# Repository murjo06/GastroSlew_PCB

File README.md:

# GastroSlew_PCB
PCB deisng files for GastroSlew, running FOC

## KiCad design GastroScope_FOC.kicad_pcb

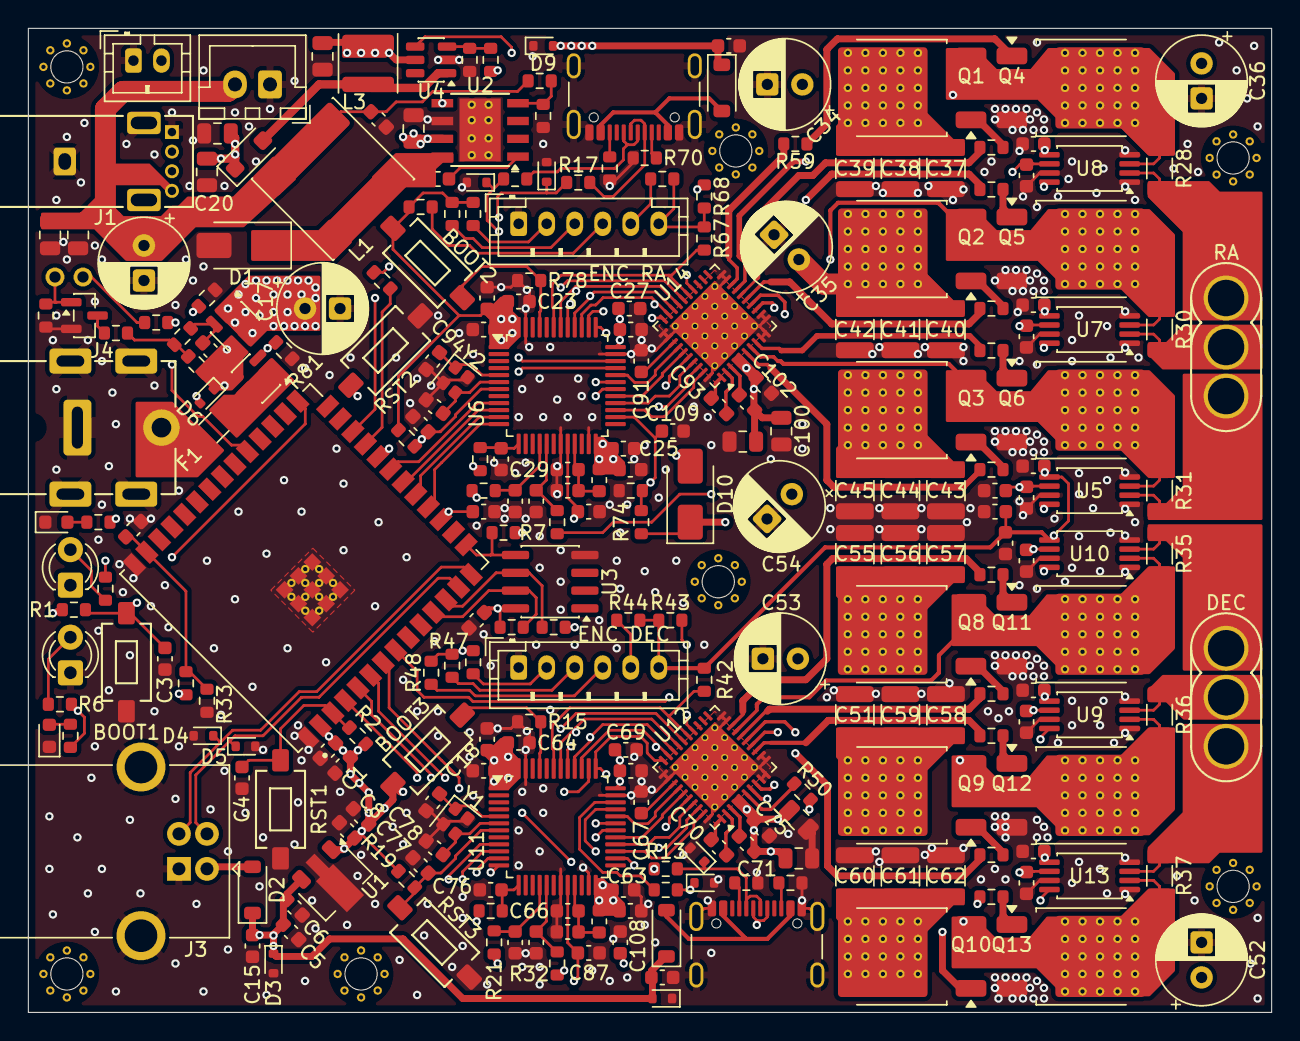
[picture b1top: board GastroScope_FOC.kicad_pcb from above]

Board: 4 copper layers, 88.8 x 70.2 mm, 257 parts (0 on the bottom side), 154 nets.

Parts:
BOOT1, BOOT2, BOOT3: TS3625X; SW_SPST_6.0x3.5
C1, C5, C8, C15, C16, C26, C27, C28, C30, C50, C68, C69, C72, C80, C98, C105, C107: 10u; C_0603_1608Metric
C2, C3, C4, C6, C7, C18, C19, C22, C23, C24, C25, C29, C31, C32, C46, C47, C49, C63, C64, C65, C66, C75, C77, C81, C82, C83, C87, C88, C89, C90, C92, C99, C102, C104: 100n; C_0603_1608Metric
C9: 2u2; C_0603_1608Metric
C10, C103, C106, C108, C109: 10n; C_0603_1608Metric
C11, C20, C21, C73, C85, C86, C100, C101: 10u; C_0805_2012Metric
C12, C13: 22u; C_0805_2012Metric
C14, C17, C34, C35, C36, C52, C53, C54: 330u; CP_Radial_D6.3mm_P2.50mm
C33, C48, C74, C76, C84, C97: 2n2; C_0603_1608Metric
C37, C38, C39, C40, C41, C42, C43, C44, C45, C51, C55, C56, C57, C58, C59, C60, C61, C62: 22u; C_1210_3225Metric
C67, C71, C91, C96: 1u; C_0603_1608Metric
C70, C93: 47n; C_0603_1608Metric
C78, C79, C94, C95: 12p; C_0603_1608Metric
D1, D10: SS34; D_SMA
D2, D12, D18: 1N5819HW-7-F; D_SOD-123
D3, D4, D5, D9, D13, D14, D17, D19, D20: LESD5D5.0CT1G; D_SOD-523
D6: BZT52C12T; D_SOD-523
D7, D15: LED; LED_0603_1608Metric
D8, D16: LED; LED_D3.0mm
D11: DSS34; D_SOD-123F
F1: 4A; Fuse_1206_3216Metric
J1: USB_A; USB_A_sideways
J2: VOUT; JST_XH_B2B-XH-A_1x02_P2.50mm_Vertical
J3: USB_B; USB_B_OST_USB-B1HSxx_Horizontal
J4: VIN; Connector_BarrelJack_HighCurrent
J5, J9: MOTOR; Connector_MR-30
J6, J8: USB_C_Receptacle_USB2.0_14P; USB_C_Receptacle_GCT_USB4105-xx-A_16P_TopMnt_Horizontal
J7, J10: ENCODER; JST_PH_B6B-PH-K_1x06_P2.00mm_Vertical
L1: 15u; L_APV_ANR8040
L2, L5: 120R; L_0603_1608Metric
L3: 15u; L_APV_ANR4030
L4: BRAKE; JST_PH_B2B-PH-K_1x02_P2.00mm_Vertical
MCU1: ESP32-S3-WROOM-1U; XCVR_ESP32-S3-WROOM-1U-N4R2
Q1, Q2, Q3, Q4, Q5, Q6, Q8, Q9, Q10, Q11, Q12, Q13: IRLR7821TRLPBF; DPAK_TO-252
Q7: AO3400A; SOT-23
Q14, Q15: SP40P28TS; STO-23-6-PMOS
R1, R2, R3, R9, R15, R19, R41, R42, R43, R44, R47, R48, R66, R67, R68, R69, R72, R73, R78, R79, R80: 10k; R_0603_1608Metric
R4: 3k24; R_0603_1608Metric
R5, R6, R89: 330R; R_0603_1608Metric
R7, R8: 4k7; R_0603_1608Metric
R10, R25: 1k; R_0603_1608Metric
R11, R26, R27, R74, R81, R86, R87, R88: 100k; R_0603_1608Metric
R12: 2k55; R_0603_1608Metric
R13, R14, R17, R18: 22R; R_0603_1608Metric
R16, R20, R21, R29, R32, R65: 100R; R_0603_1608Metric
R22, R23, R24, R49, R50, R51, R52, R53, R54, R59, R60, R61: 4R7; R_0603_1608Metric
R28, R30, R31, R35, R36, R37: R50; R_1206_3216Metric
R33, R75: 6k8; R_0603_1608Metric
R34: 0; R_0603_1608Metric
R45, R46, R70, R71: 5k1; R_0603_1608Metric
RST1, RST2, RST3: TS3625X; SW_SPST_6.0x3.5
SW1: EN; PinHeader_1x02_P2.00mm_Vertical
U1: MD7671E33PA1; SOT-89-3
U2: TPS5430DDAR; TI_SO-PowerPAD-8_ThermalVias
U3: M24C64-RMN6TP; SOIC-8_3.9x4.9mm_P1.27mm
U4: MT3608; SOT-23-6
U5, U7, U8, U9, U10, U13: INA240AxPW; TSSOP-8_4.4x3mm_P0.65mm
U6, U11: STM32G474CBTx; LQFP-48_7x7mm_P0.5mm
U12, U14: DRV8323S; QFN-40-1EP_6x6mm_P0.5mm_EP4.6x4.6mm_ThermalVias
Y1, Y2: 16MHz; Crystal_SMD_2016-4Pin_2.0x1.6mm

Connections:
/DEC/A: J9.3, R37.2, U13.3 (-)
/DEC/AADC: C76.1, R20.1, U11.13 (PA5)
/DEC/B: J9.2, R36.2, U9.3 (-)
/DEC/BADC: C84.1, R21.1, U11.16 (PB0)
/DEC/BOOT0: BOOT3.2 (B), R15.2, U11.45 (PB8)
/DEC/C: J9.1, R35.2, U10.3 (-)
/DEC/CADC: C74.1, R32.1, U11.17 (PB1)
/DEC/CS_ENC: J10.5, R44.1, U11.38 (PA14)
/DEC/CS_GATE: R43.1, U11.39 (PA15), U12.29 (nSCS)
/DEC/D+: D20.1 (A1), J8.A6 (D+), J8.B6 (D+), R14.2
/DEC/D-: D19.1 (A1), J8.A7 (D-), J8.B7 (D-), R13.2
/DEC/FAULT: R42.1, U11.43 (PB6), U12.25 (nFAULT)
/DEC/GHA: R50.1, U12.6 (GHA)
/DEC/GHB: R51.1, U12.15 (GHB)
/DEC/GHC: R49.1, U12.16 (GHC)
/DEC/GLA: R54.1, U12.8 (GLA)
/DEC/GLB: R53.1, U12.13 (GLB)
/DEC/GLC: R52.1, U12.18 (GLC)
/DEC/HA: U11.32 (PA10), U12.34 (INHA)
/DEC/HB: U11.31 (PA9), U12.36 (INHB)
/DEC/HC: U11.30 (PA8), U12.38 (INHC)
/DEC/LA: U11.29 (PB15), U12.35 (INLA)
/DEC/LB: U11.28 (PB14), U12.37 (INLB)
/DEC/LC: U11.27 (PB13), U12.39 (INLC)
/DEC/MISO: J10.2, R41.1, U11.41 (PB4), U12.26 (SDO)
/DEC/MOSI: J10.3, R47.1, U11.42 (PB5), U12.27 (SDI)
/DEC/OSC_IN: C79.1, U11.5 (PF0), Y1.1
/DEC/OSC_OUT: C78.1, U11.6 (PF1), Y1.3
/DEC/RST: C77.1, R19.2, RST3.2 (B), U11.7 (PG10)
/DEC/SCLK: J10.4, R48.1, U11.40 (PB3), U12.28 (SCLK)
/DEC/SHA: Q10.3 (S), Q13.2 (D), R37.1, U12.7 (SHA), U13.2 (+)
/DEC/SHB: Q9.3 (S), Q12.2 (D), R36.1, U9.2 (+), U12.14 (SHB)
/DEC/SHC: Q8.3 (S), Q11.2 (D), R35.1, U10.2 (+), U12.17 (SHC)
/DEC/VREF: C87.2, C88.1, C89.1, C90.1, U9.6 (REF2), U10.6 (REF2), U11.20 (VREF+), U13.6 (REF2)
/EN_PWR: MCU1.31 (IO38), R89.1
/RA/A: J5.3, R31.2, U5.2 (+)
/RA/AADC: C33.1, R16.1, U6.16 (PB0)
/RA/B: J5.2, R30.2, U7.2 (+)
/RA/BADC: C48.1, R29.1, U6.17 (PB1)
/RA/BOOT0: BOOT2.2 (B), R78.2, U6.45 (PB8)
/RA/C: J5.1, R28.2, U8.2 (+)
/RA/CADC: C97.1, R65.1, U6.13 (PA5)
/RA/CS_ENC: J7.5, R69.1, U6.38 (PA14)
/RA/CS_GATE: R68.1, U6.39 (PA15), U14.29 (nSCS)
/RA/D+: D14.1 (A1), R18.2, U6.34 (PA12)
/RA/D-: D13.1 (A1), R17.2, U6.33 (PA11)
/RA/FAULT: R67.1, U6.43 (PB6), U14.25 (nFAULT)
/RA/GHA: R24.1, U14.6 (GHA)
/RA/GHB: R23.1, U14.15 (GHB)
/RA/GHC: R22.1, U14.16 (GHC)
/RA/GLA: R61.1, U14.8 (GLA)
/RA/GLB: R60.1, U14.13 (GLB)
/RA/GLC: R59.1, U14.18 (GLC)
/RA/HA: U6.32 (PA10), U14.34 (INHA)
/RA/HB: U6.31 (PA9), U14.36 (INHB)
/RA/HC: U6.30 (PA8), U14.38 (INHC)
/RA/LA: U6.29 (PB15), U14.35 (INLA)
/RA/LB: U6.28 (PB14), U14.37 (INLB)
/RA/LC: U6.27 (PB13), U14.39 (INLC)
/RA/MISO: J7.2, R66.1, U6.41 (PB4), U14.26 (SDO)
/RA/MOSI: J7.3, R72.1, U6.42 (PB5), U14.27 (SDI)
/RA/OSC_IN: C94.1, U6.5 (PF0), Y2.1
/RA/OSC_OUT: C95.1, U6.6 (PF1), Y2.3
/RA/RST: C104.1, R79.2, RST2.2 (B), U6.7 (PG10)
/RA/SCLK: J7.4, R73.1, U6.40 (PB3), U14.28 (SCLK)
/RA/SHA: Q3.3 (S), Q6.2 (D), R31.1, U5.3 (-), U14.7 (SHA)
/RA/SHB: Q2.3 (S), Q5.2 (D), R30.1, U7.3 (-), U14.14 (SHB)
/RA/SHC: Q1.3 (S), Q4.2 (D), R28.1, U8.3 (-), U14.17 (SHC)
/RA/VREF: C32.2, C46.1, C49.1, C99.1, C107.1, U5.6 (REF2), U6.20 (VREF+), U7.6 (REF2), U8.6 (REF2)
/VIN_RAW: C9.2, D6.1 (K), Q14.S, Q15.S, R26.2, R27.1, R87.1
/VPWR: F1.1, Q15.D
BUSADC: C106.2, C108.2, C109.2, MCU1.17 (IO9), R74.2, R75.1, U6.26 (PB12), U11.26 (PB12)
CHIP_PU: C4.1, MCU1.3 (EN), R2.2, RST1.2 (B)
D+: D4.1 (A1), J3.3 (D+), MCU1.14 (IO20)
D-: D5.1 (A1), J3.2 (D-), MCU1.13 (IO19)
DIR_DEC: MCU1.7 (IO7), U11.12 (PA4)
DIR_RA: MCU1.18 (IO10), U6.12 (PA4)
EN_BRAKE: MCU1.24 (IO47), U4.4 (EN)
EN_DEC: MCU1.8 (IO15), U11.37 (PA13), U12.30 (ENABLE)
EN_RA: MCU1.22 (IO14), U6.37 (PA13), U14.30 (ENABLE)
EN_SW: MCU1.23 (IO21), R34.1
Earth: BOOT1.1 (A), C1.1, C2.1, C3.2, C4.2, C5.2, C6.2, C7.2, C8.2, C11.1, C12.2, C13.2, C14.2, C15.1, C16.2, C17.2, C18.2, C19.1, C20.1, C21.2, C22.2, C23.2, C24.2, C25.2, C26.2, C27.2, C28.2, C29.1, C30.1, C31.1, C32.1, C33.2, C34.2, C35.2, C36.2, C37.2, C38.2, C39.2, C40.2, C41.2, C42.2, C43.2, C44.2, C45.2, C46.2, C47.1, C48.2, C49.2, C50.2, C51.2, C52.2, C53.2, C54.2, C55.2, C56.2, C57.2, C58.2, C59.2, C60.2, C61.2, C62.2, C63.2, C64.2, C65.2, C66.1, C67.2, C68.2, C69.2, C72.1, C73.1, C74.2, C75.1, C76.2, C77.2, C78.2, C79.2, C80.1, C81.1, C82.1, C83.1, C84.2, C85.1, C86.1, C87.1, C88.2, C89.2, C90.2, C91.2, C92.1, C94.2, C95.2, C97.2, C98.1, C99.2, C100.1, C101.1, C102.1, C103.1, C104.2, C105.2, C106.1, C107.2, C108.1, C109.1, D1.2 (A), D3.2 (A2), D4.2 (A2), D5.2 (A2), D7.1 (K), D8.1 (K), D9.1 (A1), D13.2 (A2), D14.2 (A2), D15.1 (K), D16.1 (K), D17.1 (A1), D19.2 (A2), D20.2 (A2), J1.4 (GND), J1.5 (Shield), J2.1, J3.4 (GND), J3.5 (Shield), J4.2, J6.A1 (GND), J6.A12 (GND), J6.B1 (GND), J6.B12 (GND), J6.S1 (SHIELD), J7.1, J8.A1 (GND), J8.A12 (GND), J8.B1 (GND), J8.B12 (GND), J8.S1 (SHIELD), J10.1, L4.1, MCU1.1 (GND), MCU1.40 (GND), MCU1.41_1 (GND), MCU1.41_2 (GND), MCU1.41_3 (GND), MCU1.41_4 (GND), MCU1.41_5 (GND), MCU1.41_6 (GND), MCU1.41_7 (GND), MCU1.41_8 (GND), MCU1.41_9 (GND), Q4.3 (S), Q5.3 (S), Q6.3 (S), Q7.2 (S), Q11.3 (S), Q12.3 (S), Q13.3 (S), R4.1, R12.2, R15.1, R26.1, R33.2, R45.2, R46.2, R70.2, R71.2, R75.2, R78.1, R80.2, R81.2, RST1.1 (A), RST2.1 (A), RST3.1 (A), U1.2 (GND), U2.6 (GND), U2.9 (GNDPAD), U3.4 (VSS), U4.2 (GND), U5.1 (GND), U5.4 (GND), U5.7 (REF1), U6.19 (VSSA), U6.23 (VSS), U6.35 (VSS), U6.47 (VSS), U7.1 (GND), U7.4 (GND), U7.7 (REF1), U8.1 (GND), U8.4 (GND), U8.7 (REF1), U9.1 (GND), U9.4 (GND), U9.7 (REF1), U10.1 (GND), U10.4 (GND), U10.7 (REF1), U11.19 (VSSA), U11.23 (VSS), U11.35 (VSS), U11.47 (VSS), U12.9 (SPA), U12.10 (SNA), U12.11 (SNB), U12.12 (SPB), U12.19 (SPC), U12.20 (SNC), U12.31 (CAL), U12.32 (AGND), U12.40 (PGND), U12.41 (PGND), U13.1 (GND), U13.4 (GND), U13.7 (REF1), U14.9 (SPA), U14.10 (SNA), U14.11 (SNB), U14.12 (SPB), U14.19 (SPC), U14.20 (SNC), U14.31 (CAL), U14.32 (AGND), U14.40 (PGND), U14.41 (PGND), Y1.2, Y1.4, Y2.2, Y2.4
GPIO0: BOOT1.2 (B), C3.1, MCU1.27 (IO0), R1.2
unnamed: C9.1, Q14.G, R86.1
unnamed: C10.2, D1.1 (K), L1.1, U2.8 (PH)
unnamed: D2.2 (A), J3.1 (VBUS)
unnamed: D6.2 (A), Q15.G, R81.1
unnamed: D7.2 (A), R5.1
unnamed: D8.2 (A), R6.1
unnamed: D11.2 (A), L3.2, U4.1 (SW)
unnamed: C20.2, C86.2, D11.1 (K), L4.2, R11.1
unnamed: D12.2 (A), J6.A4 (VBUS), J6.A9 (VBUS), J6.B4 (VBUS), J6.B9 (VBUS)
unnamed: D15.2 (A), R10.1
unnamed: D16.2 (A), R25.1
unnamed: D18.2 (A), J8.A4 (VBUS), J8.A9 (VBUS), J8.B4 (VBUS), J8.B9 (VBUS)
unnamed: C12.1, C13.1, C14.1, C16.1, J1.1 (VBUS), J2.2, L1.2, R3.1
unnamed: F1.2, J4.1
unnamed: J6.A5 (CC1), R70.1
unnamed: J6.B5 (CC2), R71.1
unnamed: J6.A6 (D+), J6.B6 (D+), R18.1
unnamed: J6.A7 (D-), J6.B7 (D-), R17.1
unnamed: J8.A5 (CC1), R45.1
unnamed: J8.B5 (CC2), R46.1
unnamed: C103.2, MCU1.39 (IO1), R27.2, R33.1
unnamed: Q1.1 (G), R22.2
unnamed: Q2.1 (G), R23.2
unnamed: Q3.1 (G), R24.2
unnamed: Q4.1 (G), R59.2
unnamed: Q5.1 (G), R60.2
unnamed: Q6.1 (G), R61.2
unnamed: Q7.3 (D), R88.2
unnamed: Q7.1 (G), R80.1, SW1.1 (A)
unnamed: Q8.1 (G), R49.2
unnamed: Q9.1 (G), R51.2
unnamed: Q10.1 (G), R50.2
unnamed: Q11.1 (G), R52.2
unnamed: Q12.1 (G), R53.2
unnamed: Q13.1 (G), R54.2
unnamed: R16.2, U5.8
unnamed: R20.2, U13.8
unnamed: R21.2, U9.8
unnamed: R29.2, U7.8
unnamed: R32.2, U10.8
unnamed: R65.2, U8.8
unnamed: R86.2, R87.2, R88.1
unnamed: R89.2, SW1.2 (B)
unnamed: C10.1, U2.1 (BOOT)
unnamed: R34.2, U2.5 (EN)
unnamed: R3.2, R4.2, U2.4 (VSENSE)
unnamed: R11.2, R12.1, U4.3 (FB)
unnamed: C29.2, C30.2, L5.1, U6.21 (VDDA)
unnamed: R13.1, U11.33 (PA11)
unnamed: R14.1, U11.34 (PA12)
unnamed: C66.2, C80.2, L2.1, U11.21 (VDDA)
unnamed: C70.2, U12.2 (CPH)
unnamed: C70.1, U12.1 (CPL)
unnamed: C67.1, U12.33 (DVDD)
unnamed: C71.1, U12.3 (VCP)
unnamed: C93.2, U14.2 (CPH)
unnamed: C93.1, U14.1 (CPL)
unnamed: C91.1, U14.33 (DVDD)
unnamed: C96.1, U14.3 (VCP)
RX_DEC: MCU1.6 (IO6), U11.11 (PA3)
RX_RA: MCU1.19 (IO11), U6.11 (PA3)
SCL: MCU1.12 (IO8), R8.1, U3.6 (SCL)
SDA: MCU1.15 (IO3), R7.1, U3.5 (SDA)
STEP_DEC: MCU1.4 (IO4), U11.9 (PA1)
STEP_RA: MCU1.21 (IO13), U6.9 (PA1)
TX_DEC: MCU1.5 (IO5), U11.10 (PA2)
TX_RA: MCU1.20 (IO12), U6.10 (PA2)
VCC: BOOT2.1 (A), BOOT3.1 (A), C1.2, C2.2, C7.1, C8.1, C18.1, C19.2, C22.1, C23.1, C24.1, C25.1, C26.1, C27.1, C28.1, C31.2, C47.2, C50.1, C63.1, C64.1, C65.1, C68.1, C69.1, C81.2, C82.2, C83.2, C92.2, C105.1, D10.2 (A), J7.6, J10.6, L2.2, L5.2, MCU1.2 (3V3), R1.1, R2.1, R5.2, R6.2, R7.2, R8.2, R9.2, R19.1, R41.2, R42.2, R43.2, R44.2, R47.2, R48.2, R66.2, R67.2, R68.2, R69.2, R72.2, R73.2, R79.1, U1.1 (VO), U3.8 (VDD), U5.5 (V+), U6.1 (VBAT), U6.24 (VDD), U6.36 (VDD), U6.48 (VDD), U7.5 (V+), U8.5 (V+), U9.5 (V+), U10.5 (V+), U11.1 (VBAT), U11.24 (VDD), U11.36 (VDD), U11.48 (VDD), U12.24 (VREF), U13.5 (V+), U14.24 (VREF)
VIN: C11.2, C17.1, C21.1, C34.1, C35.1, C36.1, C37.1, C38.1, C39.1, C40.1, C41.1, C42.1, C43.1, C44.1, C45.1, C51.1, C52.1, C53.1, C54.1, C55.1, C56.1, C57.1, C58.1, C59.1, C60.1, C61.1, C62.1, C71.2, C73.2, C75.2, C85.2, C96.2, C100.2, C101.2, C102.2, D10.1 (K), L3.1, Q1.2 (D), Q2.2 (D), Q3.2 (D), Q8.2 (D), Q9.2 (D), Q10.2 (D), Q14.D, R10.2, R25.2, R74.1, U2.7 (VIN), U4.5 (IN), U12.4 (VM), U12.5 (VDRAIN), U14.4 (VM), U14.5 (VDRAIN)
VUSB: C5.1, C6.1, C15.2, C72.2, C98.2, D2.1 (K), D3.1 (A1), D9.2 (A2), D12.1 (K), D17.2 (A2), D18.1 (K), U1.3 (VI)
WC: MCU1.11 (IO18), R9.1, U3.7 (WP)

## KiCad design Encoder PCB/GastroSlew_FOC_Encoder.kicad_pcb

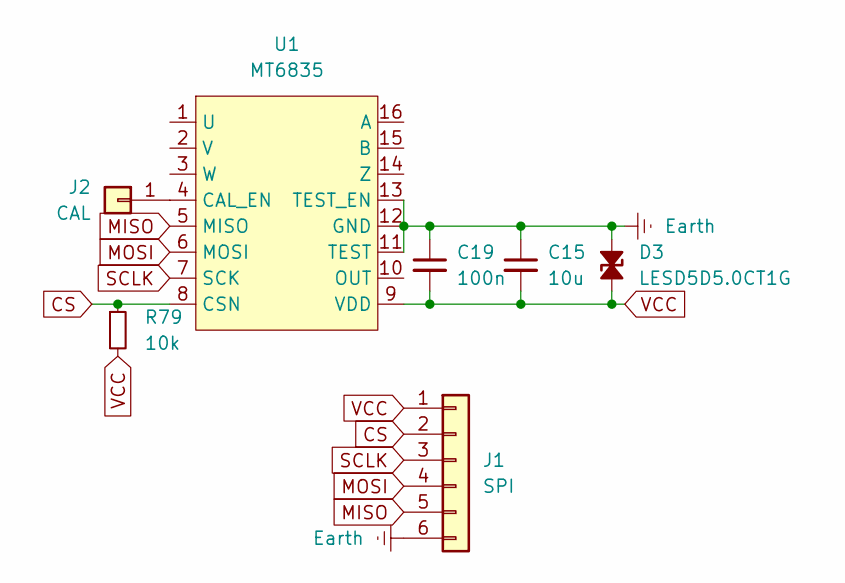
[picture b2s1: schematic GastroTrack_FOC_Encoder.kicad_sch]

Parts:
C15: 10u; C_0603_1608Metric; LCSC C7432767
C19: 100n; C_0603_1608Metric; LCSC C14663
D3: LESD5D5.0CT1G; D_SOD-523; LCSC C5199850
J1: SPI; Connector_PH_2.0mm_SMD_6P
J2: CAL; PinHeader_1x01_P2.54mm_Vertical
R79: 10k; R_0603_1608Metric; LCSC C5126214
U1: MT6835; TSSOP-16_4.4x5mm_P0.65mm

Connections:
CS: J1.2, R79.1, U1.8 (CSN)
Earth: C15.1, C19.1, D3.1 (A1), J1.6, U1.11 (TEST), U1.12 (GND), U1.13 (TEST_EN)
MISO: J1.5, U1.5 (MISO)
MOSI: J1.4, U1.6 (MOSI)
unnamed: J2.1, U1.4 (CAL_EN)
SCLK: J1.3, U1.7 (SCK)
VCC: C15.2, C19.2, D3.2 (A2), J1.1, R79.2, U1.9 (VDD)

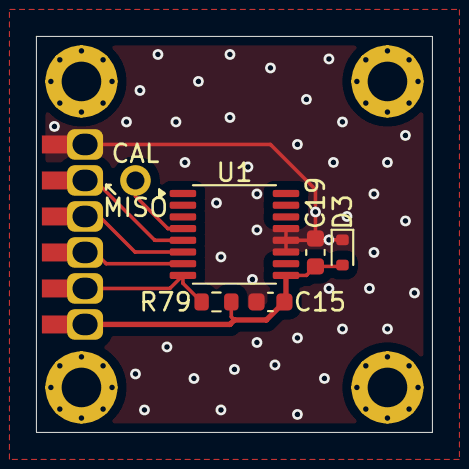
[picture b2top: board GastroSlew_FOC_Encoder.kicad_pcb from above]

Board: 2 copper layers, 22.0 x 22.0 mm, 7 parts (0 on the bottom side), 7 nets.
